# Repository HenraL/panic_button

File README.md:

<!-- 
-- +==== BEGIN AsperHeader =================+
-- LOGO:
--               @@@@@@@@@
--            @@@@       @@@@
--           @@  @@@@@@@@@  @@
--             @@@  @@@  @@@
--               @@@@@@@@@
--               @@ @@@ @@
--                 @@@@@
--                   @
--                  @@@
--                 @- #@
--                 @: @@
--                  @ @
--                  @ @
--                  @ @
--                 -@ @:
--                 =@ @*
--                 ## -#
--               %@@@@%@@@
--               @       @@
--            -@%@@@@#%@@@@@+
--         @@%+             =%@%#
--      =@@.                    @@#
--     %@:                       *@@-
--   *@*                           *%%
--  #@=         .   +*=             +@%
--  @*         :@@@@+-+@@@=          *@
-- %@          @@-        @@%         @@
-- %@         @%  %@@-@@@  #@         @@
-- @+        %@= @@     @@  @@        +@
-- @+        *@- @@     @@ -@%        +@
-- %@         @%  =@@@@@#  #@         @@
-- *@:         @@%       *@@+        :@%
--  @#           @%@*+@@%@#          #@
--  #@%                           . #@*
--    @%                           %@
--     @%@                       @@%
--      -@@%                   #@@=
--         *@@@             @@@#
--             @%@@@@@@@@@@@+
-- /STOP
-- PROJECT: AsperHeader
-- FILE: README.md
-- CREATION DATE: 14-08-2026
-- LAST Modified: 2:57:22 14-08-2026
-- DESCRIPTION:
-- A small panic beacon: reports its position to a server, falls back to SMS when unreachable, and advertises BLE (Find My-style) so phones can interact with it without an app.
-- /STOP
-- COPYRIGHT: (c) Asperguide
-- PURPOSE: This is the file in charge of introducing the repository.
-- // AR
-- +==== END AsperHeader =================+
-->
# Panic Button

A small **panic beacon** (target: no bigger than a finger; a palm if that size can't be
reached) that:

1. Updates its position towards a server.
2. If that is not available, sends an SMS (or similar).
3. Regardless of the above, advertises a BLE beacon (Apple Find My-style, Android hub,
   Samsung if they stray) so nearby phones can interact with it without any app.

Apple UWB is out of reach (proprietary Apple U1/U2 chip + MFi program) — phone interaction is
BLE only. Cost target: **< $50 / unit** (excluding the IoT/SIM plan).

## Repository layout

- `AGENTS.md` — rules and conventions for AI agents and contributors; read it first.
- `KiCad/v1/panic_button` — first board attempt (archive).
- `KiCad/v2/dev/panic_button_dev` — dev variant of the v2 circuit.
- `KiCad/v2/tiny/panic_button_tiny` — **active design** (KiCad 10): the tiny variant,
  as small as possible.
- `KiCad/v2/tiny/bom.md` — live bill of materials (strictly the BOM).
- `KiCad/v2/tiny/design.md` — design decisions, notes and open questions.
- `platformio/` — firmware (PlatformIO + Arduino on ESP32-C3). Comes **after** the circuit
  planning, not in parallel.
- `bonus/` — tools / environments / scratch (`bonus/tmp/`).

## Hardware status

- **Tiny** (active): ESP32-C3 (BLE) + SIM7670G LTE Cat1 (GNSS, SMS, HTTP/MQTT), Li-ion +
  USB-C charging, wake-on-motion accelerometer. Schematic in progress in KiCad 10.
- **Dev** = the tiny circuit + test infrastructure (test points, button array, richer LEDs,
  AirM2M Core ESP32-C3 module as the easier-to-mount MCU), functionally identical.

See `bom.md` for parts and prices, `design.md` for decisions.

## License

MIT — see `LICENSE`.

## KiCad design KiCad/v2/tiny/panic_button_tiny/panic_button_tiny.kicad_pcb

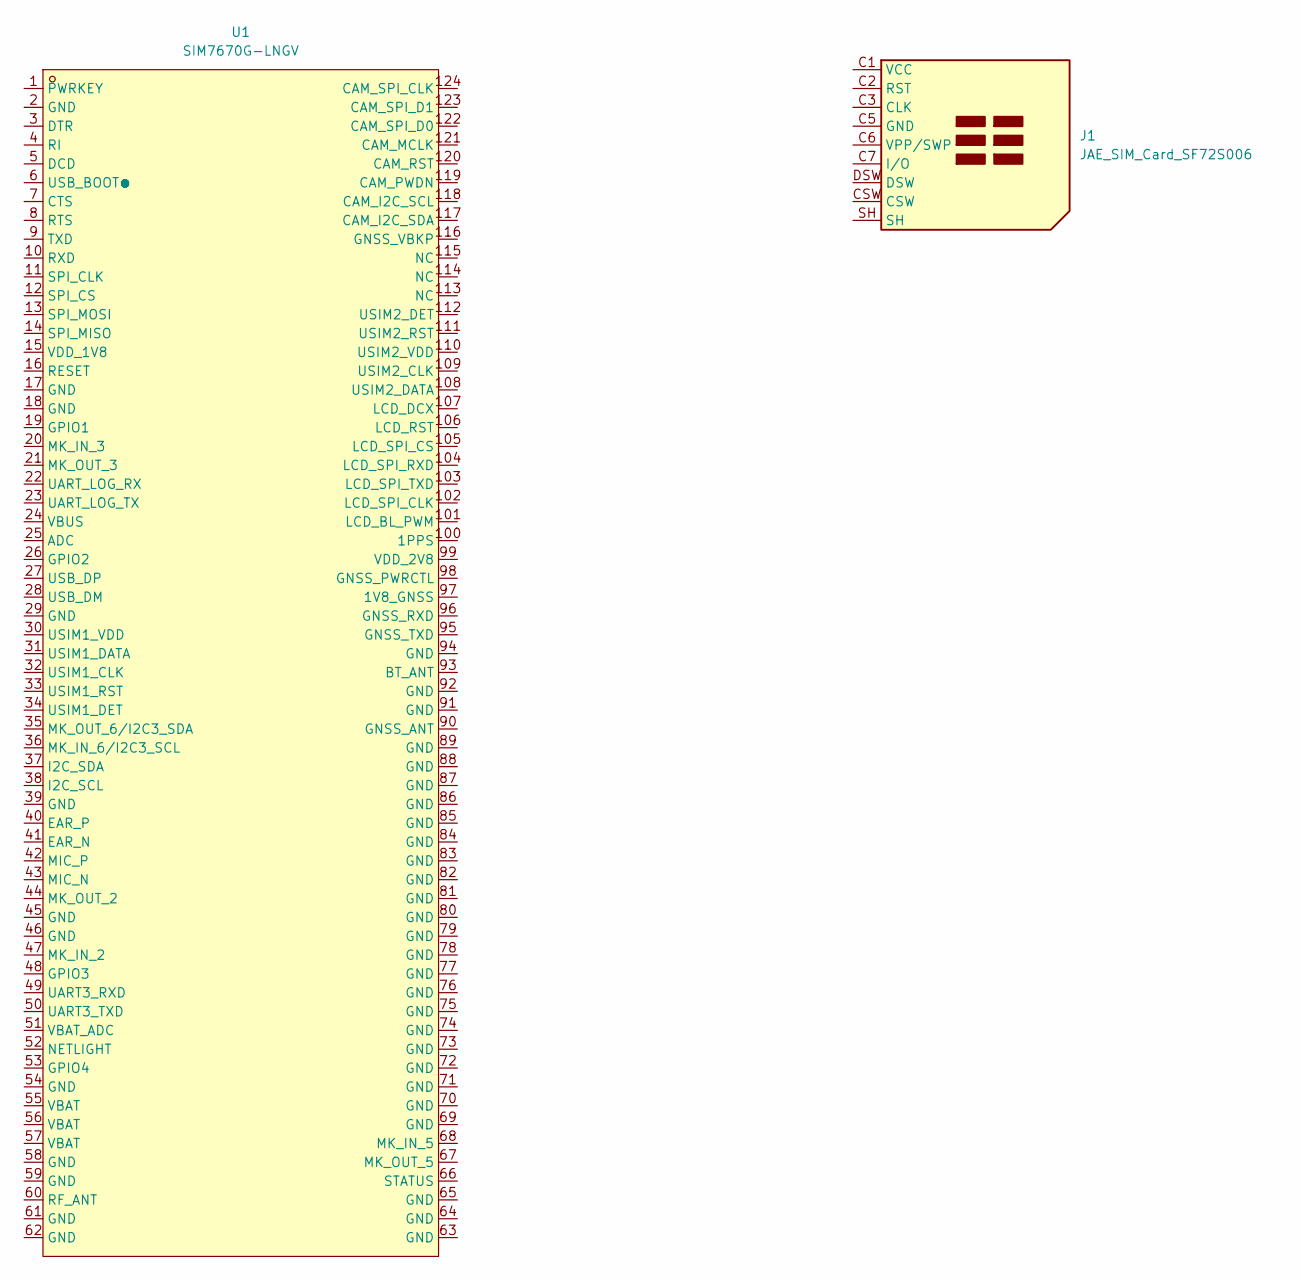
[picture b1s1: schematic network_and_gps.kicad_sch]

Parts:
J1: JAE_SIM_Card_SF72S006
U1: SIM7670G-LNGV; LCC-124_L24.0-W24.0-P1.0-TL; MPN SIM7670G-LNGV; LCSC Part C45935408

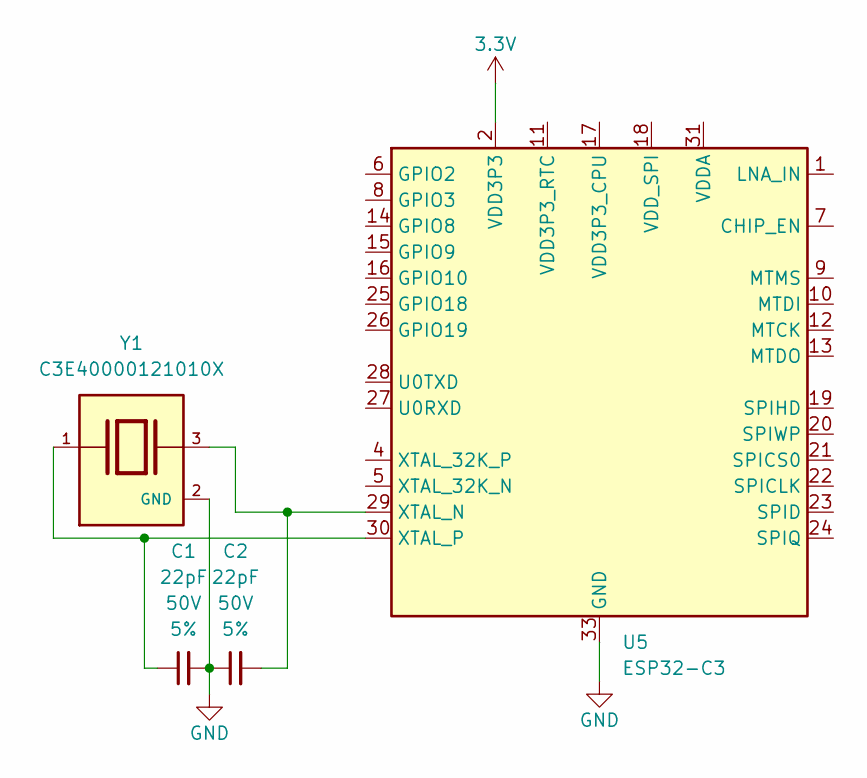
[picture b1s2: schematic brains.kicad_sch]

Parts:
C1, C2: 22pF; C_0402_1005Metric; Voltage 50V; Tolerance 5%
U5: ESP32-C3; QFN-32-1EP_5x5mm_P0.5mm_EP3.7x3.7mm
Y1: C3E40000121010X; XTAL_C3E40000121010X; PARTREV August 01, 2022

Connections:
3.3V: U5.2 (VDD3P3), U5.3 (VDD3P3); also elsewhere on the board
GND: C1.2, C2.1, U5.33 (GND), Y1.2 (GND), Y1.4 (GND); also elsewhere on the board
unnamed: U5.31 (VDDA), U5.32 (VDDA)
unnamed: C2.2, U5.29 (XTAL_N), Y1.3
unnamed: C1.1, U5.30 (XTAL_P), Y1.1

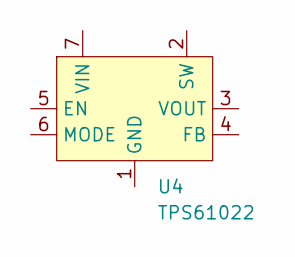
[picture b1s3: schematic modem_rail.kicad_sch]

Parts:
U4: TPS61022; Texas_RWU0007A_VQFN-7_2x2mm_P0.5mm

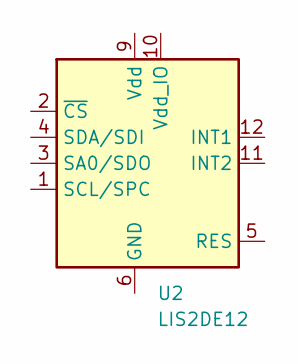
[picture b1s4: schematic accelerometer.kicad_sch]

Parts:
U2: LIS2DE12; LGA-12_2x2mm_P0.5mm

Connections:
unnamed: U2.6 (GND), U2.7 (GND), U2.8 (GND)

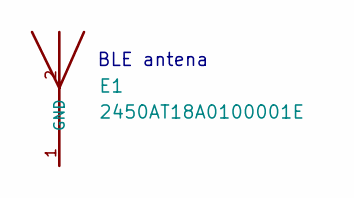
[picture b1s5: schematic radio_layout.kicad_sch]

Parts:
E1: 2450AT18A0100001E; XCVR_2450AT18A0100001E; PARTREV 4.0

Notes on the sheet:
BLE antena

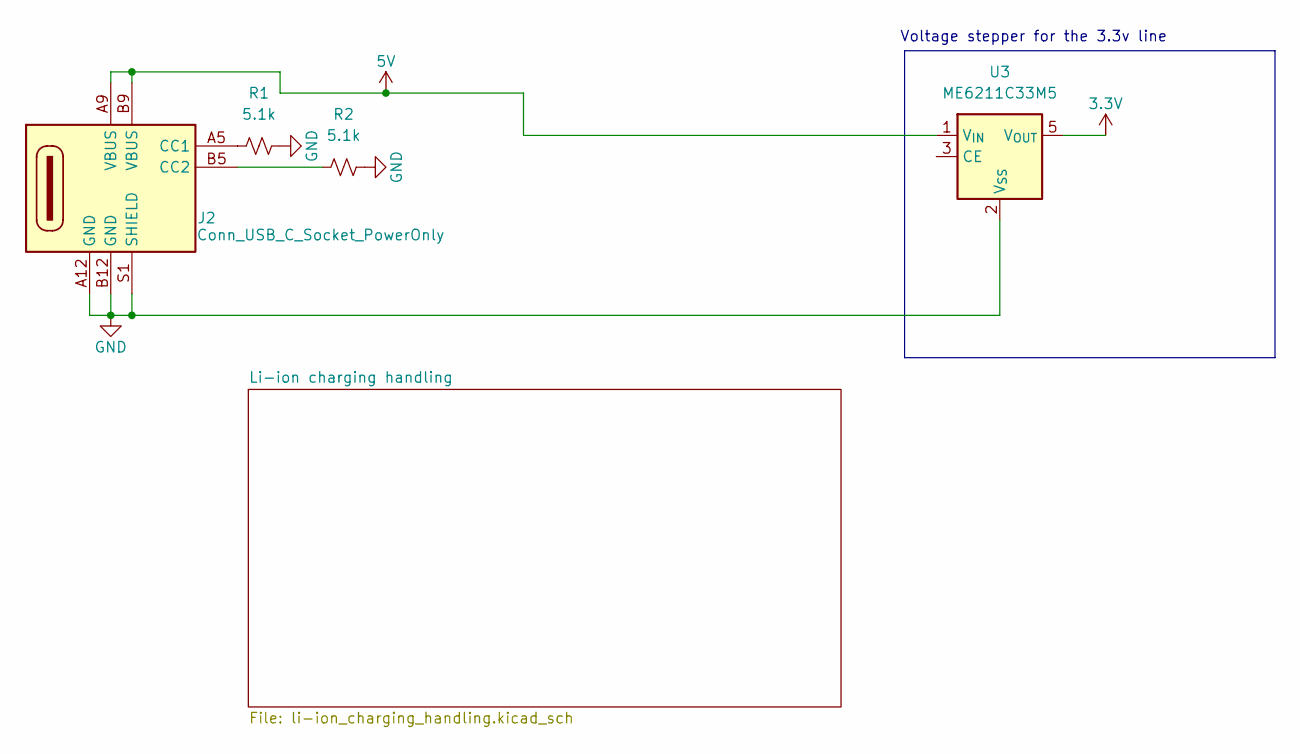
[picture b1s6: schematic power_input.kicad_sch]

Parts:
J2: Conn_USB_C_Socket_PowerOnly; Conn_USB_C_Socket_GCT_USB4125-GF-A-0190
R1, R2: 5.1k; R_0402_1005Metric
U3: ME6211C33M5; SOT-23-5

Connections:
3.3V: U3.5 (V_{OUT}); also elsewhere on the board
5V: J2.A9 (VBUS), J2.B9 (VBUS), U3.1 (V_{IN})
GND: J2.A12 (GND), J2.B12 (GND), J2.S1 (SHIELD), R1.2, R2.2, U3.2 (V_{SS}); also elsewhere on the board
unnamed: J2.A5 (CC1), R1.1
unnamed: J2.B5 (CC2), R2.1

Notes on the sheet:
Voltage stepper for the 3.3v line

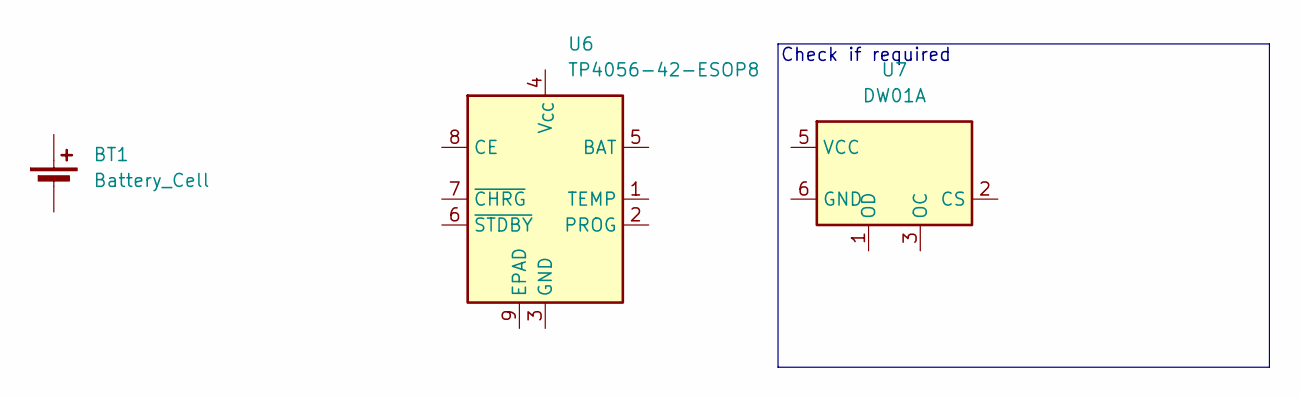
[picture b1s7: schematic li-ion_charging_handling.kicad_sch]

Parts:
BT1: Battery_Cell; JST_EH_S2B-EH_1x02_P2.50mm_Horizontal
U6: TP4056-42-ESOP8; SOIC-8-1EP_3.9x4.9mm_P1.27mm_EP2.41x3.3mm_ThermalVias
U7: DW01A; SOT-23-6

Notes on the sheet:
Check if required

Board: 2 copper layers, 16 parts (0 on the bottom side), 9 nets, no tracks yet.

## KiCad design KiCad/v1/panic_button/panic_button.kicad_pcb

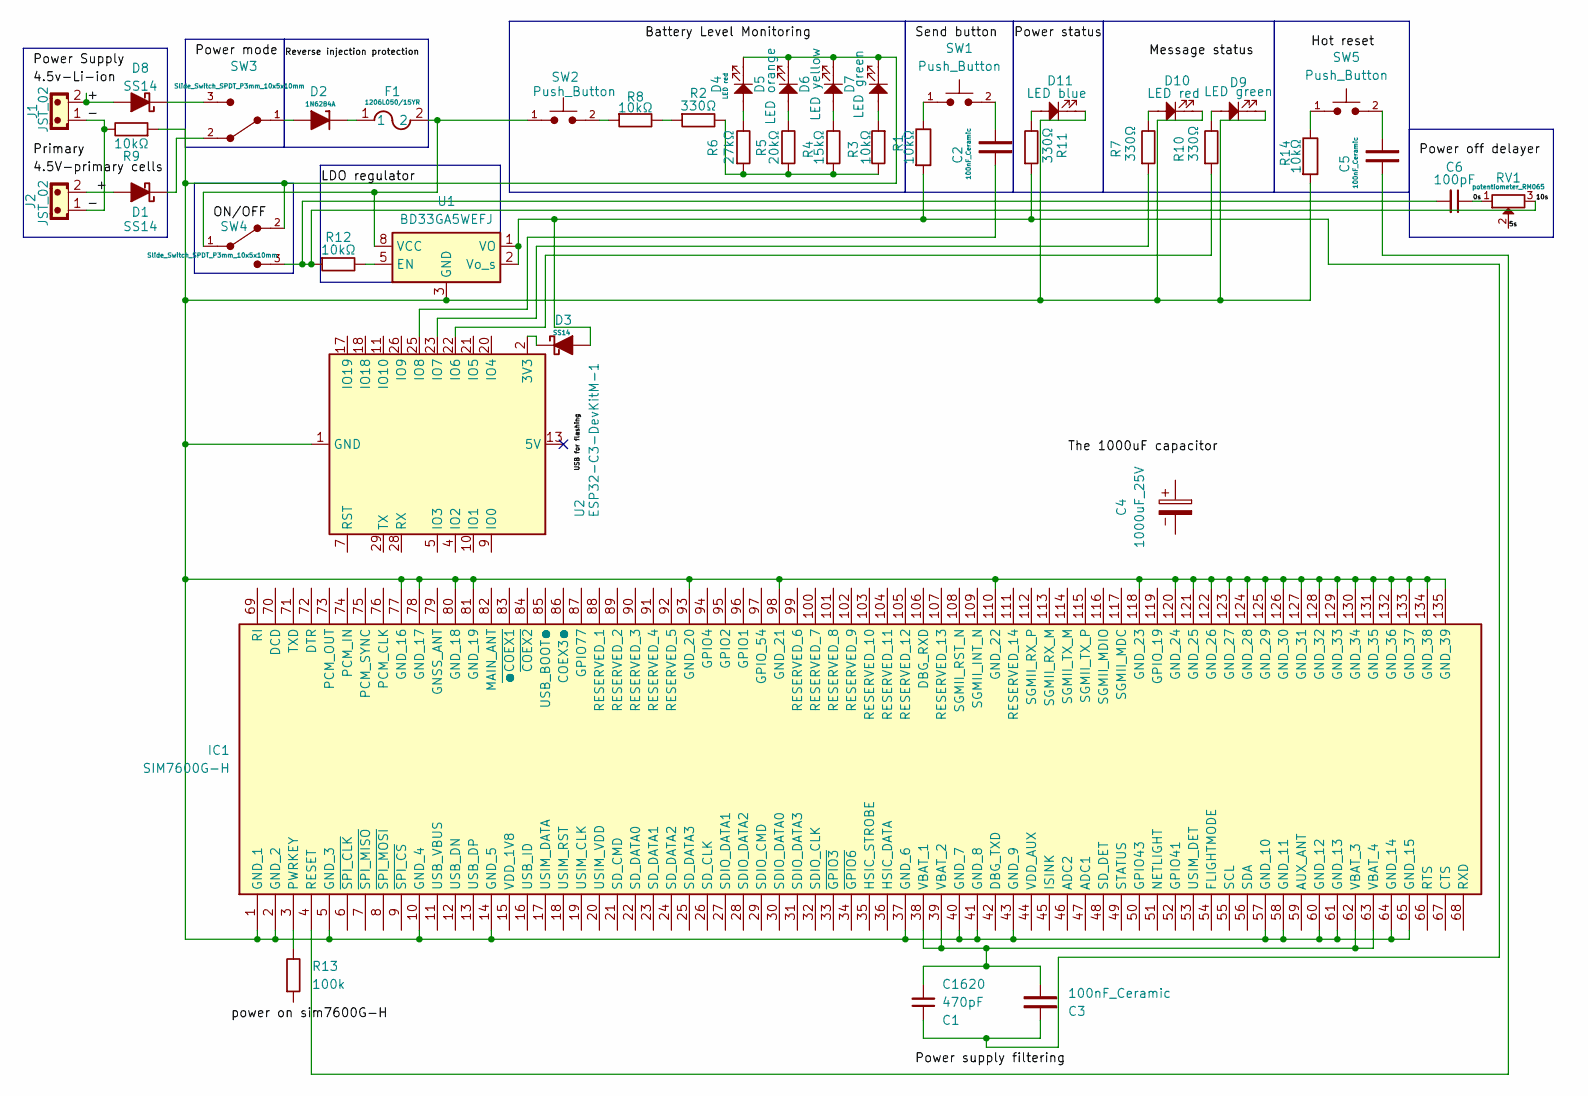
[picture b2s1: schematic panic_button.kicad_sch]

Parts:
C1: 470pF_0603_25V; C_0603_1608Metric; Part Number C0603C471J5GACTU; JLCPCB ID C1620
C2, C3, C5: 100nF_Ceramic; C_Disc_D5.0mm_W2.5mm_P2.50mm
C4: 1000uF_25V; CP_Radial_D13.0mm_P5.00mm
C6: 100pF_0603_50V; C_0603_1608Metric; Part Number CC0603JRNPO9BN101; JLCPCB ID C14858
D1, D3, D8: SS14; D_SMA
D2: 1N6284A; D_DO-201_P12.70mm_Horizontal_Zener
D4, D10: LED red; LED_D5.0mm
D5: LED orange; LED_D5.0mm
D6: LED yellow; LED_D5.0mm
D7, D9: LED green; LED_D5.0mm
D11: LED blue; LED_D5.0mm
F1: 1206L050/15YR; 1206LSeries_LTF
IC1: SIM7600G-H; SIM7600GH; Manufacturer_Part_Number SIM7600G-H
J1, J2: JST_02; JST_EH_B2B-EH-A_1x02_P2.50mm_Vertical
R1, R14: 10k_0402; R_0402_1005Metric; Part Number RT0402FRE0710KL
R2, R7, R10, R11: 330Ω; R_Axial_DIN0207_L6.3mm_D2.5mm_P10.16mm_Horizontal
R3, R8, R9, R12: 10kΩ; R_Axial_DIN0207_L6.3mm_D2.5mm_P10.16mm_Horizontal
R4: 15kΩ; R_Axial_DIN0207_L6.3mm_D2.5mm_P10.16mm_Horizontal
R5: 20kΩ; R_Axial_DIN0207_L6.3mm_D2.5mm_P10.16mm_Horizontal
R6: 27kΩ; R_Axial_DIN0207_L6.3mm_D2.5mm_P10.16mm_Horizontal
R13: 100k; R_Axial_DIN0207_L6.3mm_D2.5mm_P10.16mm_Horizontal
RV1: potentiometer_RM065; Potentiometer_RM065
SW1, SW2, SW5: Push_Button; SW_PUSH_6mm
SW3, SW4: Slide_Switch_SPDT_P3mm_10x5x10mm
U1: BD33GA5WEFJ; HTSOP-8-1EP_3.9x4.9mm_P1.27mm_EP2.4x3.2mm
U2: ESP32-C3-DevKitM-1

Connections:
/0s: C6.1, RV1.1
/5s: RV1.2
/10s: C6.2, R12.1, RV1.3, SW4.3
/+: D1.2 (A), D8.2 (A), J1.2, J2.2
/-: J1.1, J2.1, R9.2
/LDO regulator: D4.1, D5.1, D6.1, D7.1, D9.1, D10.1, D11.1, IC1.1 (GND_1), IC1.2 (GND_2), IC1.5 (GND_3), IC1.10 (GND_4), IC1.14 (GND_5), IC1.37 (GND_6), IC1.40 (GND_7), IC1.41 (GND_8), IC1.43 (GND_9), IC1.57 (GND_10), IC1.58 (GND_11), IC1.60 (GND_12), IC1.61 (GND_13), IC1.64 (GND_14), IC1.65 (GND_15), IC1.77 (GND_16), IC1.78 (GND_17), IC1.80 (GND_18), IC1.81 (GND_19), IC1.93 (GND_20), IC1.98 (GND_21), IC1.110 (GND_22), IC1.118 (GND_23), IC1.120 (GND_24), IC1.121 (GND_25), IC1.122 (GND_26), IC1.123 (GND_27), IC1.124 (GND_28), IC1.125 (GND_29), IC1.126 (GND_30), IC1.127 (GND_31), IC1.128 (GND_32), IC1.129 (GND_33), IC1.130 (GND_34), IC1.131 (GND_35), IC1.132 (GND_36), IC1.133 (GND_37), IC1.134 (GND_38), IC1.135 (GND_39), R9.1, R14.2, SW4.2, U1.3 (GND), U1.4 (GND), U1.6 (GND), U1.7 (GND), U1.9 (GND), U2.1 (GND), U2.6 (GND), U2.8 (GND), U2.12 (GND), U2.15 (GND), U2.16 (GND), U2.19 (GND), U2.24 (GND), U2.27 (GND), U2.30 (GND)
unnamed: C2.1, SW1.2
unnamed: C5.1, SW5.2
unnamed: D1.1 (K), SW3.2
unnamed: D2.2 (A), SW3.1
unnamed: D2.1 (K), F1.1
unnamed: C1.1, C3.1, D3.2 (A), R1.2, R11.1, U1.1 (VO), U1.2 (Vo_s)
unnamed: D3.1 (K), U2.2 (3V3), U2.3 (3V3)
unnamed: D4.2, R6.2
unnamed: D5.2, R5.2
unnamed: D6.2, R4.2
unnamed: D7.2, R3.1
unnamed: D8.1 (K), SW3.3
unnamed: D9.2, R10.2
unnamed: D10.2, R7.2
unnamed: D11.2, R11.2
unnamed: IC1.3 (PWRKEY), R13.2
unnamed: C5.2, IC1.4 (RESET)
unnamed: C1.2, C3.2, IC1.38 (VBAT_1), IC1.39 (VBAT_2), IC1.62 (VBAT_3), IC1.63 (VBAT_4)
unnamed: R1.1, SW1.1
unnamed: R2.1, R8.2
unnamed: R2.2, R3.2, R4.1, R5.1, R6.1
unnamed: R8.1, SW2.2
unnamed: R14.1, SW5.1
unnamed: R12.2, U1.5 (EN)
unnamed: F1.2, SW2.1, SW4.1, U1.8 (VCC)
unnamed: R10.1, U2.22 (IO6)
unnamed: R7.1, U2.23 (IO7)
unnamed: C2.2, U2.25 (IO8)

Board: 2 copper layers, 43 parts (0 on the bottom side), 33 nets, no tracks yet.
